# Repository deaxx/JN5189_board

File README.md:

# JN5189_board
mini-dev board on E180-Z8910SX

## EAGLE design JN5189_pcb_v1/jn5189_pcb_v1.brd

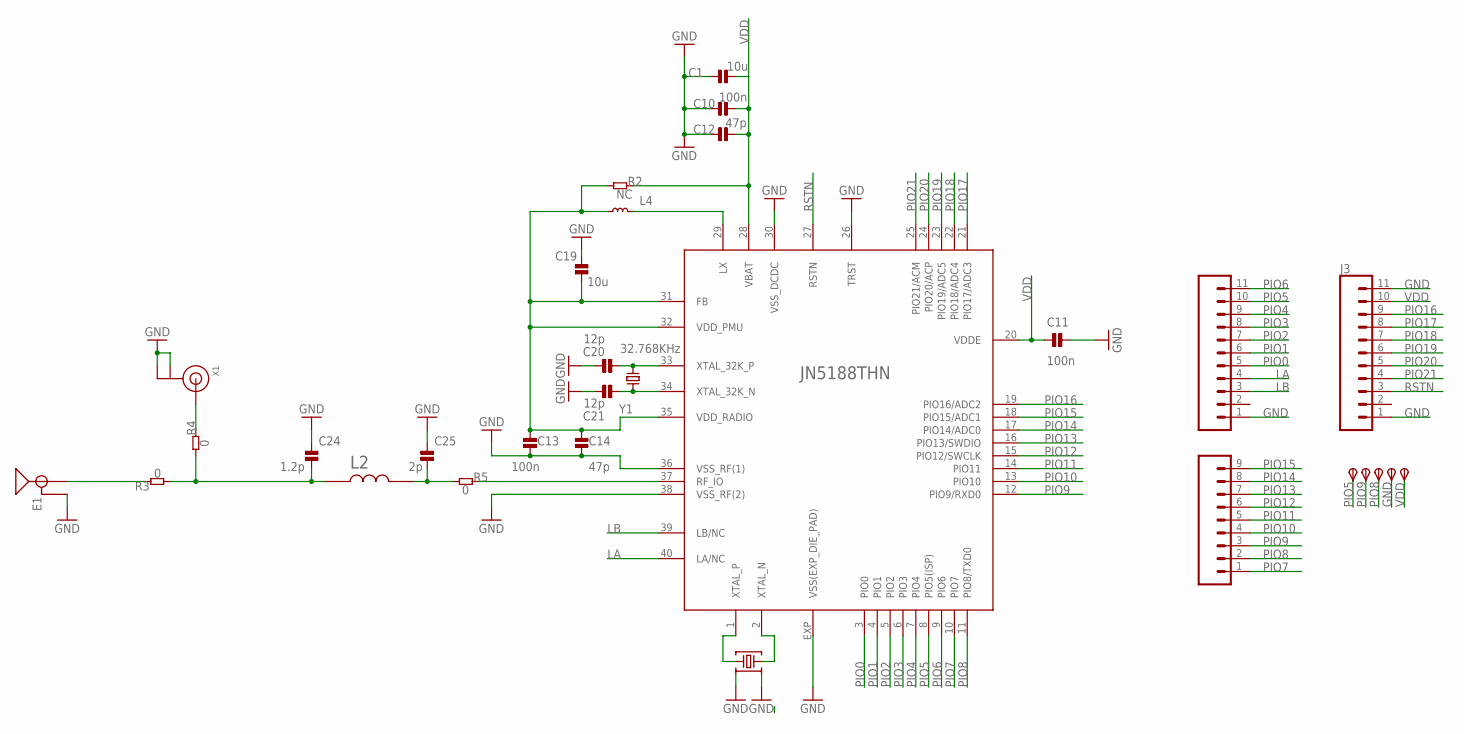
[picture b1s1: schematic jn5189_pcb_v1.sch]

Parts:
3V3: TPSTP11R; TP11R
C1, C19: 10u; _PKG_C_0805
C10, C11, C13: 100n; _PKG_C_0402
C12, C14: 47p; _PKG_C_0402
C20, C21: 12p; _PKG_C_0402
C24: 1.2p; _PKG_C_0402
C25: 2p; _PKG_C_0402
E1: ANTENNA-GROUNDEDTRACE-15.2MM; TRACE_ANTENNA_2.4GHZ_15.2MM
GND: TPSTP11R; TP11R
ISP: TPSTP11R; TP11R
J1, J3: CONN_11_1.27MM; 1X11-1.27MM
J2: CONN_051.27MM; 1X05_1.27MM
L2: 3.3n; INDC1005X40N
L4: 4.7uH; _PKG_C_0805
R2: NC; _PKG_C_0402
R3, R4, R5: 0; _PKG_C_0402
RXD: TPSTP11R; TP11R
TXD: TPSTP11R; TP11R
U$1: JN5188THN
X1: ANTENNA_U.FL; U.FL
Y1: 32.768KHz; XTAL-2P-3215
Y2: 32Mhz; XTAL-4P-2016

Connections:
GND: C1.1, C10.2, C11.1, C12.2, C13.1, C14.1, C19.1, C20.1, C21.1, C24.2, C25.2, E1.GND, GND.TP, J1.1, J3.1, J3.11, U$1.26 (TRST), U$1.30 (VSS_DCDC), U$1.36 (VSS_RF(1)), U$1.38 (VSS_RF(2)), U$1.EXP (VSS(EXP_DIE_PAD)), X1.1 (GND), X1.2 (GND), Y2.2, Y2.4
LA: J1.4, U$1.40 (LA/NC)
LB: J1.3, U$1.39 (LB/NC)
unnamed: L4.2, U$1.29 (LX)
unnamed: U$1.1 (XTAL_P), Y2.1
unnamed: U$1.2 (XTAL_N), Y2.3
unnamed: C13.2, C14.2, C19.2, L4.1, R2.2, U$1.31 (FB), U$1.32 (VDD_PMU), U$1.35 (VDD_RADIO)
unnamed: R5.1, U$1.37 (RF_IO)
unnamed: C25.1, L2.2, R5.2
unnamed: C24.1, L2.1, R3.2, R4.2
unnamed: R4.1, X1.3 (SIGNAL)
unnamed: E1.ANT (SIGNAL), R3.1
PIO0: J1.5, U$1.3 (PIO0)
PIO1: J1.6, U$1.4 (PIO1)
PIO2: J1.7, U$1.5 (PIO2)
PIO3: J1.8, U$1.6 (PIO3)
PIO4: J1.9, U$1.7 (PIO4)
PIO5: ISP.TP, J1.10, U$1.8 (PIO5(ISP))
PIO6: J1.11, U$1.9 (PIO6)
PIO7: J2.1, U$1.10 (PIO7)
PIO8: J2.2, TXD.TP, U$1.11 (PIO8/TXD0)
PIO9: J2.3, RXD.TP, U$1.12 (PIO9/RXD0)
PIO10: J2.4, U$1.13 (PIO10)
PIO11: J2.5, U$1.14 (PIO11)
PIO12: J2.6, U$1.15 (PIO12/SWCLK)
PIO13: J2.7, U$1.16 (PIO13/SWDIO)
PIO14: J2.8, U$1.17 (PIO14/ADC0)
PIO15: J2.9, U$1.18 (PIO15/ADC1)
PIO16: J3.9, U$1.19 (PIO16/ADC2)
PIO17: J3.8, U$1.21 (PIO17/ADC3)
PIO18: J3.7, U$1.22 (PIO18/ADC4)
PIO19: J3.6, U$1.23 (PIO19/ADC5)
PIO20: J3.5, U$1.24 (PIO20/ACP)
PIO21: J3.4, U$1.25 (PIO21/ACM)
RSTN: J3.3, U$1.27 (RSTN)
VDD: 3V3.TP, C1.2, C10.1, C11.2, C12.1, J3.10, R2.1, U$1.20 (VDDE), U$1.28 (VBAT)
X32K_Q1: C20.2, U$1.33 (XTAL_32K_P), Y1.1
X32K_Q2: C21.2, U$1.34 (XTAL_32K_N), Y1.2

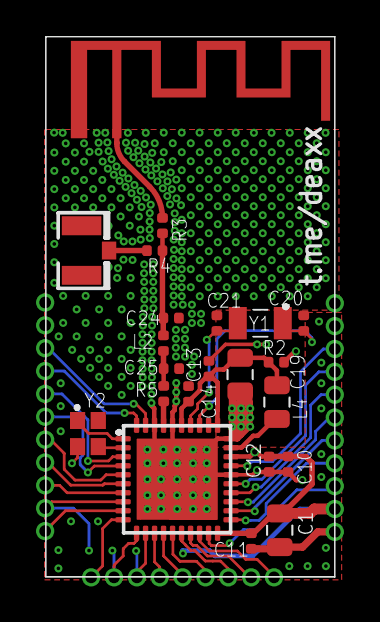
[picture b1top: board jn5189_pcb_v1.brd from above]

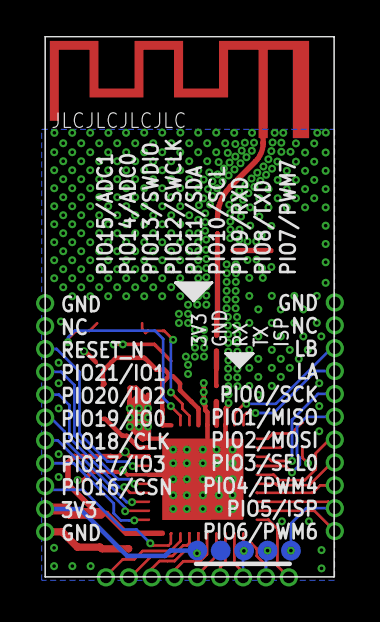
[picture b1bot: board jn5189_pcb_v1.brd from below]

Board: 4 copper layers, 16.1 x 30.0 mm, 30 parts (5 on the bottom side), 38 nets.

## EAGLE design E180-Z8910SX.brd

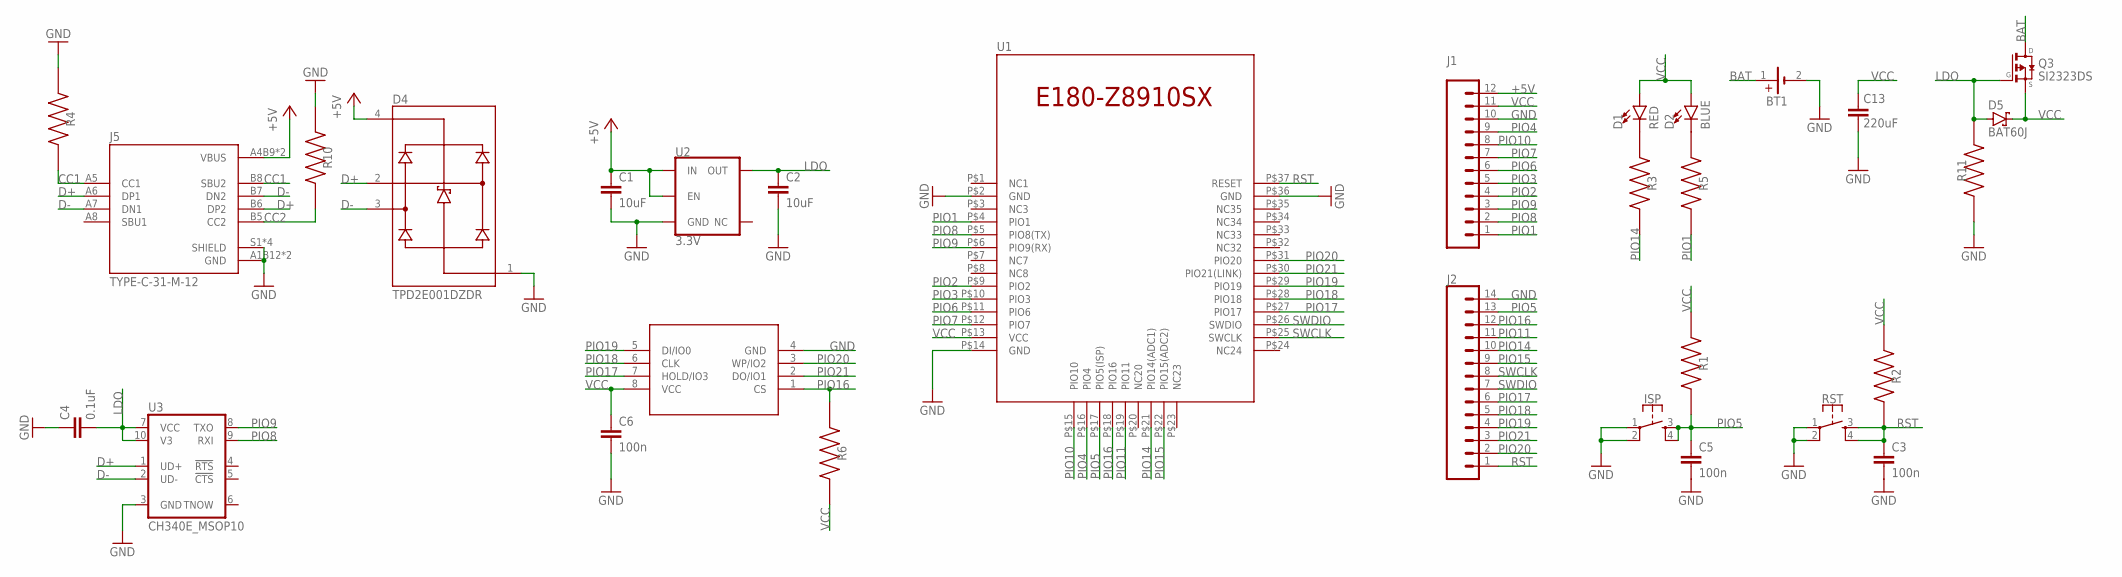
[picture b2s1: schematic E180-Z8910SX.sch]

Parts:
BT1: 79527141
C1, C2: 10uF; 0603
C3, C5, C6: 100n; 0603
C4: 0.1uF; 0603
C13: 220uF; CAPM7343X310
D1: RED; LED-0603
D2: BLUE; LED-0603
D4: TPD2E001DZDR; SOT192P237X122-4N
D5: BAT60J; SOD323_ST
ISP: MOMENTARY-SWITCH-SPST-2-SMD-4.6X2.8MM; TACTILE_SWITCH_SMD_4.6X2.8MM
J1: CONN_12NO_SILK; 1X12_NO_SILK
J2: CONN_14NO_SILK; 1X14_NO_SILK
J5: TYPE-C-31-M-12; HRO_TYPE-C-31-M-12
Q3: SI2323DS; SOT23
R1, R2, R11: 10k; RESC1005X40N
R3, R5: 2k; RESC1005X40N
R4, R10: 5.1k; RESC1005X40N
R6: 100k; RESC1005X40N
RST: MOMENTARY-SWITCH-SPST-2-SMD-4.6X2.8MM; TACTILE_SWITCH_SMD_4.6X2.8MM
U1: E180-Z8910SXE180-Z8910SP; E180-Z8910SX
U2: 3.3V; SOT23-5
U3: CH340E_MSOP10; MSOP10
U$1: W25Q80DVSNIG; SO-8

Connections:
+5V: C1.1, D4.4 (VCC), J1.12, J5.A4B9 (VBUS), J5.B4A9 (VBUS), U2.1 (IN), U2.3 (EN)
BAT: BT1.1 (+), Q3.3 (D)
CC1: J5.A5 (CC1), J5.B8 (SBU2), R4.2
CC2: J5.B5 (CC2), R10.2
D+: D4.2 (IO1), J5.A6 (DP1), J5.B6 (DP2), U3.1 (UD+)
D-: D4.3 (IO2), J5.A7 (DN1), J5.B7 (DN2), U3.2 (UD-)
GND: BT1.2 (-), C1.2, C2.2, C3.2, C4.1, C5.2, C6.2, C13.2, D4.1 (GND), ISP.1, ISP.2, J1.10, J2.14, J5.A1B12 (GND), J5.B1A12 (GND), J5.S1 (SHIELD), J5.S2 (SHIELD), J5.S3 (SHIELD), J5.S4 (SHIELD), R4.1, R10.1, R11.1, RST.1, RST.2, U1.P$2 (GND), U1.P$14 (GND), U1.P$36 (GND), U2.2 (GND), U3.3 (GND), U$1.4 (GND)
LDO: C2.1, C4.2, D5.A, Q3.1 (G), R11.2, U2.5 (OUT), U3.7 (VCC), U3.10 (V3)
unnamed: D1.C, R3.1
unnamed: D2.C, R5.1
PIO1: J1.1, R5.2, U1.P$4 (PIO1)
PIO2: J1.4, U1.P$9 (PIO2)
PIO3: J1.5, U1.P$10 (PIO3)
PIO4: J1.9, U1.P$16 (PIO4)
PIO5: C5.1, ISP.3, ISP.4, J2.13, R1.2, U1.P$17 (PIO5(ISP))
PIO6: J1.6, U1.P$11 (PIO6)
PIO7: J1.7, U1.P$12 (PIO7)
PIO8: J1.2, U1.P$5 (PIO8(TX)), U3.9 (RXI)
PIO9: J1.3, U1.P$6 (PIO9(RX)), U3.8 (TXO)
PIO10: J1.8, U1.P$15 (PIO10)
PIO11: J2.11, U1.P$19 (PIO11)
PIO14: J2.10, R3.2, U1.P$21 (PIO14(ADC1))
PIO15: J2.9, U1.P$22 (PIO15(ADC2))
PIO16: J2.12, R6.1, U1.P$18 (PIO16), U$1.1 (CS)
PIO17: J2.6, U1.P$27 (PIO17), U$1.7 (HOLD/IO3)
PIO18: J2.5, U1.P$28 (PIO18), U$1.6 (CLK)
PIO19: J2.4, U1.P$29 (PIO19), U$1.5 (DI/IO0)
PIO20: J2.2, U1.P$31 (PIO20), U$1.3 (WP/IO2)
PIO21: J2.3, U1.P$30 (PIO21(LINK)), U$1.2 (DO/IO1)
RST: C3.1, J2.1, R2.2, RST.3, RST.4, U1.P$37 (RESET)
SWCLK: J2.8, U1.P$25 (SWCLK)
SWDIO: J2.7, U1.P$26 (SWDIO)
VCC: C6.1, C13.1, D1.A, D2.A, D5.C, J1.11, Q3.2 (S), R1.1, R2.1, R6.2, U1.P$13 (VCC), U$1.8 (VCC)

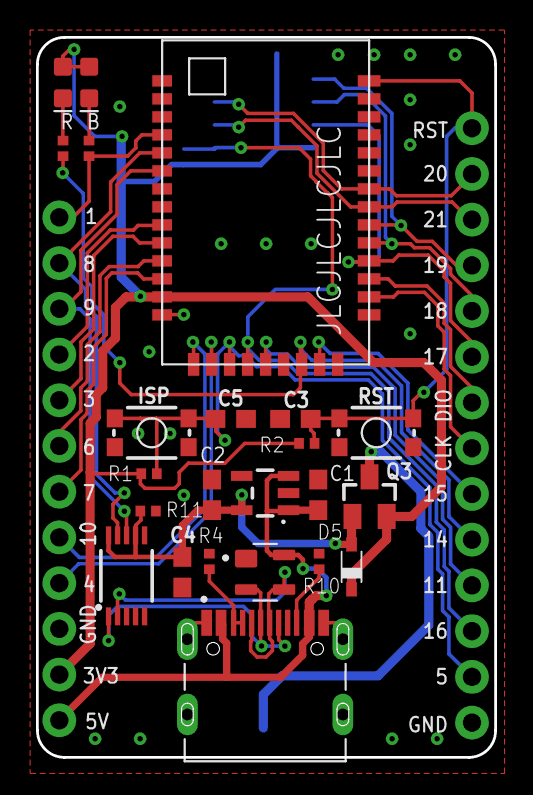
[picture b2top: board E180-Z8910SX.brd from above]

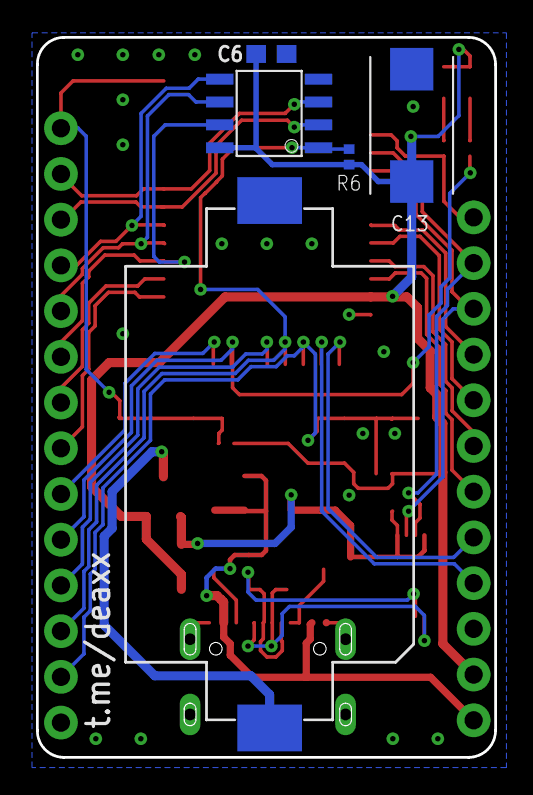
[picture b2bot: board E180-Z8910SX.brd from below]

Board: 2 copper layers, 25.5 x 40.0 mm, 30 parts (5 on the bottom side), 33 nets.

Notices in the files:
parts and their libraries:
SparkFun-IC-Power: Licensing: Creative Commons ShareAlike 4.0 International - https://creativecommons.org/licenses/by-sa/4.0
